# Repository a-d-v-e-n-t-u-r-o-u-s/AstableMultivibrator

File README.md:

# AstableMultivibrator
Astable Multivibrator project

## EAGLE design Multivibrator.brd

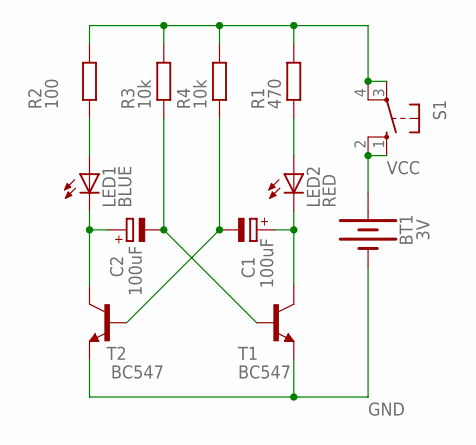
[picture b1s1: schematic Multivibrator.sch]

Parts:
BT1: 3V; BATTCOM_20MM_PTH
C1, C2: 100uF; E2,5-5
LED1: BLUE; LED5MM
LED2: RED; LED5MM
R1: 470; 0207/10
R2: 100; 0207/10
R3, R4: 10k; 0207/10
S1: 10-XX; B3F-10XX
T1, T2: BC547; TO92

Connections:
GND: BT1.2 (-), T1.1 (E), T2.1 (E)
unnamed: BT1.1 (+), S1.1 (S), S1.2 (S1)
unnamed: LED1.A, R2.1
unnamed: C2.+, LED1.K (C), T2.3 (C)
unnamed: C2.-, R3.1, T1.2 (B)
unnamed: C1.-, R4.1, T2.2 (B)
unnamed: C1.+, LED2.K (C), T1.3 (C)
unnamed: LED2.A, R1.1
VCC: R1.2, R2.2, R3.2, R4.2, S1.3, S1.4 (P1)

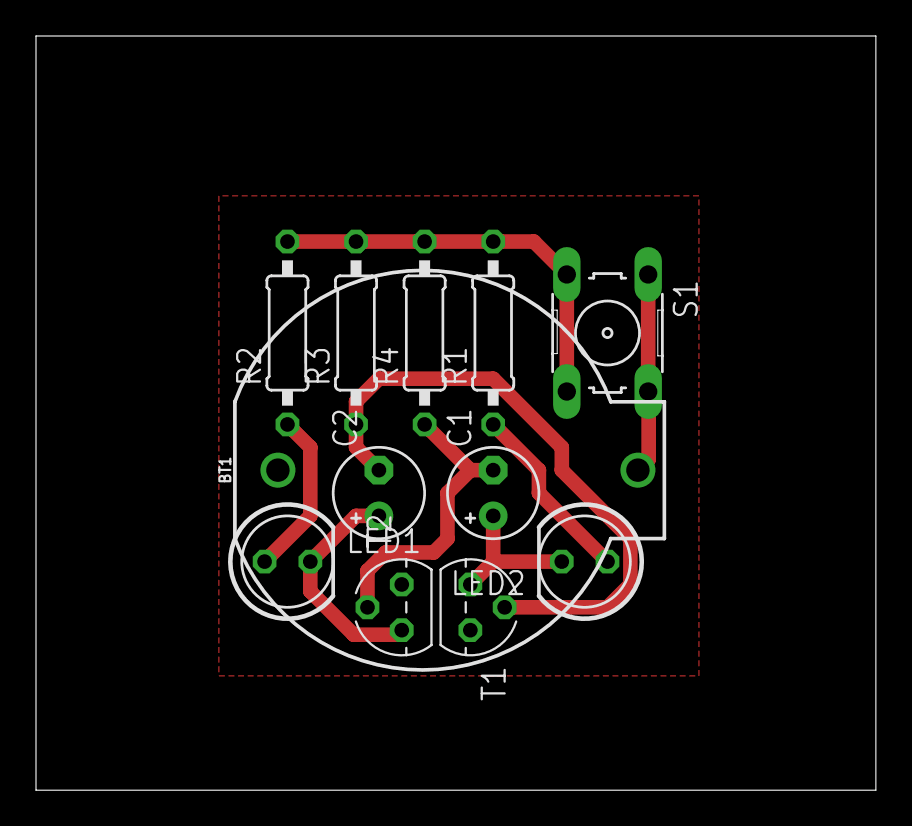
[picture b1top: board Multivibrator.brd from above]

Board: 2 copper layers, 46.7 x 41.9 mm, 12 parts (0 on the bottom side), 9 nets.

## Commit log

2018-10-16 Initialization commit
2018-10-16 Add first schematic, board and pdf files

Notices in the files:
parts and their libraries:
SparkFun-Batteries: Licensing: Creative Commons ShareAlike 4.0 International - https://creativecommons.org/licenses/by-sa/4.0
